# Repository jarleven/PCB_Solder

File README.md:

### PCB DIY manufacturing and soldering

```
Requirements
  Board size
  Labels for:
      LED
      DIP switch
      
      Name
      EidVGS 2022
      Project "Setebelte"
      Graphics
        https://gfwilliams.github.io/svgtoeagle/
        https://linuxhint.com/convert-png-to-svg-inkscape/#:~:text=In%20Inkscape%2C%20you%20can%20not,on%20how%20to%20do%20that.
      
      https://www.svgrepo.com/svg/253118/seatbelt
      https://www.flaticon.com/free-icon/seat-belt_271884

      Seatbelt icon clumsy howto :-)
      https://autode.sk/3DX8VwU
      
  ```

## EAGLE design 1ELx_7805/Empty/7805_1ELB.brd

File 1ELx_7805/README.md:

### Nedlastingar (Høgreklikk på link)
#### 3D Models
* [78xx 3D Model](https://raw.githubusercontent.com/jarleven/PCB_Solder/main/1ELx_7805/3D-Models/TO220HEATSINK.step "download")

* [Kondensator 3D Model](https://raw.githubusercontent.com/jarleven/PCB_Solder/main/1ELx_7805/3D-Models/E5-8,5.step "download")

* [Rekkeklemme 3D Model](https://raw.githubusercontent.com/jarleven/PCB_Solder/main/1ELx_7805/3D-Models/W237-132.step "download")

#### Skjema

* [Eagle schematic](https://github.com/jarleven/PCB_Solder/raw/main/1ELx_7805/Empty/7805_1ELB.sch
 "download")

### Voltage regulator datasheet

* [78xx Voltage regulator datasheet](https://www.st.com/resource/en/datasheet/l78.pdf "download")

### Schematic example

### Board example

### Fusion360 3D model of the board

### Some resources for PCB CAD and prototyping

Parts search engine (Requires registration)
https://componentsearchengine.com/

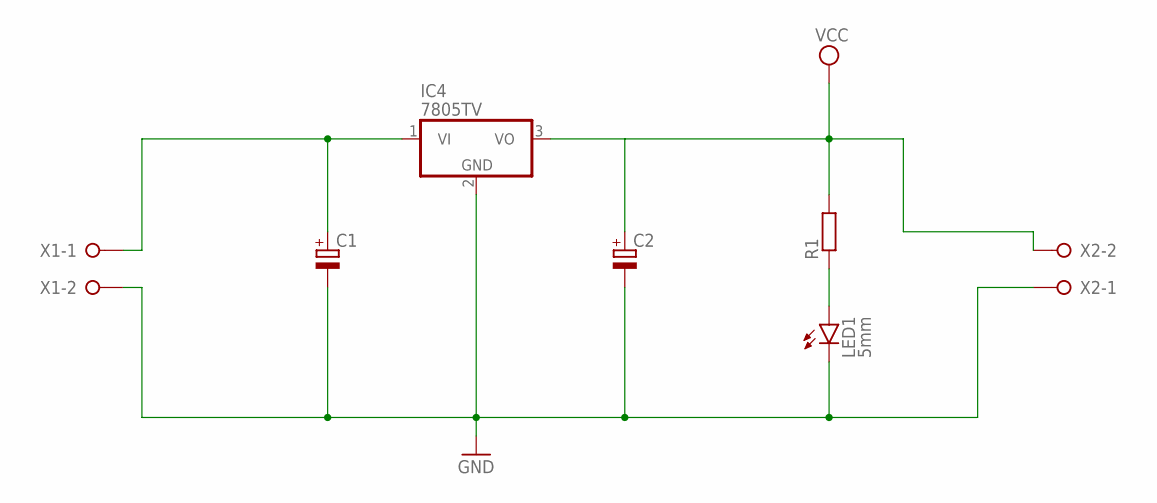
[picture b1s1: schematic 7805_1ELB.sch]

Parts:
C1, C2: CPOL-EUE5-8.5; E5-8,5
IC4: 7805TV; TO220V
LED1: 5mm; LED5MM
R1: R-EU_0207/10; 0207/10
X1, X2: W237-02P; W237-132

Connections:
GND: C1.-, C2.-, IC4.2 (GND), LED1.K (C), X1.2, X2.1
unnamed: C1.+, IC4.1 (VI), X1.1
unnamed: LED1.A, R1.1
VCC: C2.+, IC4.3 (VO), R1.2, X2.2

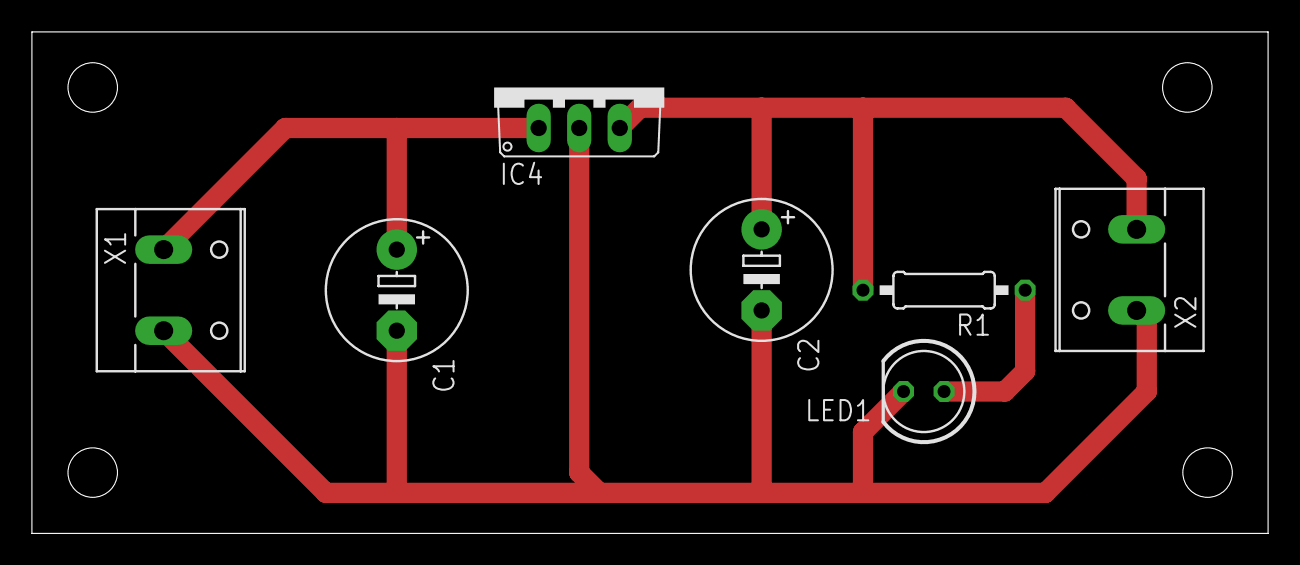
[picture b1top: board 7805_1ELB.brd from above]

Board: 2 copper layers, 77.5 x 31.4 mm, 7 parts (0 on the bottom side), 4 nets.

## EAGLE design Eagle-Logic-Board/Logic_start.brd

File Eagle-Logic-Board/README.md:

### Simple Autodesk Eagle design for logic

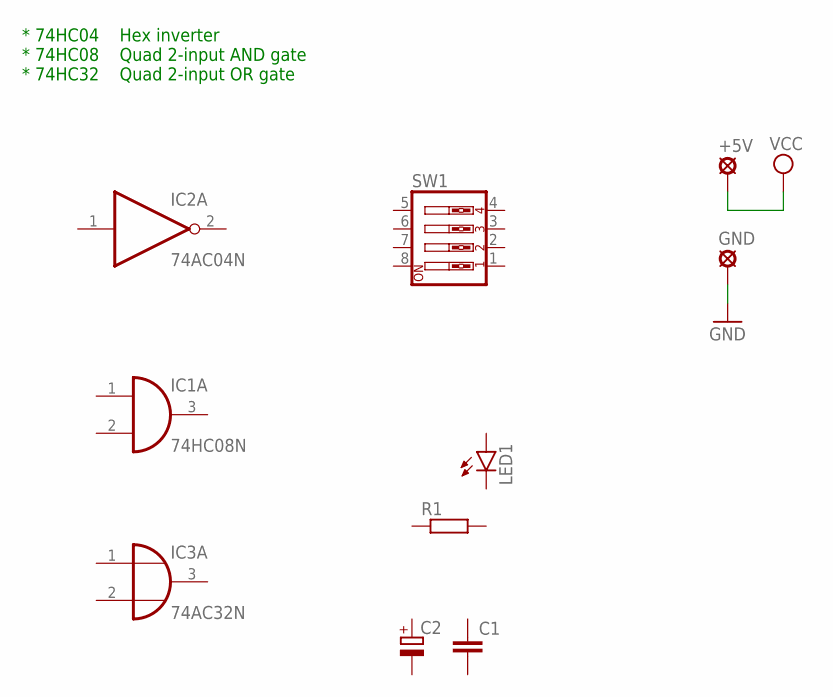
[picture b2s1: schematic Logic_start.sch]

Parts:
+5V: LSP11
C1: C-EUC1206; C1206
C2: CPOL-EUE3.5-8; E3,5-8
GND: LSP11
IC1: 74HC08N; DIL14
IC2: 74AC04N; DIL14
IC3: 74AC32N; DIL14
LED1: LED5MM
R1: R-EU_0309/10; 0309/10
SW1: SW_DIP-4; EDG-04

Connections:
GND: GND.MP, IC1.7 (GND), IC2.7 (GND), IC3.7 (GND)
VCC: +5V.MP, IC1.14 (VCC), IC2.14 (VCC), IC3.14 (VCC)

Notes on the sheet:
* 74HC04 Hex inverter * 74HC08 Quad 2-input AND gate * 74HC32 Quad 2-input OR gate

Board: 2 copper layers, 10 parts (0 on the bottom side), 2 nets, no tracks yet.

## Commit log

2022-09-18 Add files via upload
    65mm x 65mm board
2023-01-04 An empty 7805 project
2023-01-04 Cleaned out NETs
2023-01-04 Added images
2023-01-04 Removed custom 3D models
2023-01-04 The libeay32.dll issue
2023-01-04 Documentation
2023-01-04 LM317
